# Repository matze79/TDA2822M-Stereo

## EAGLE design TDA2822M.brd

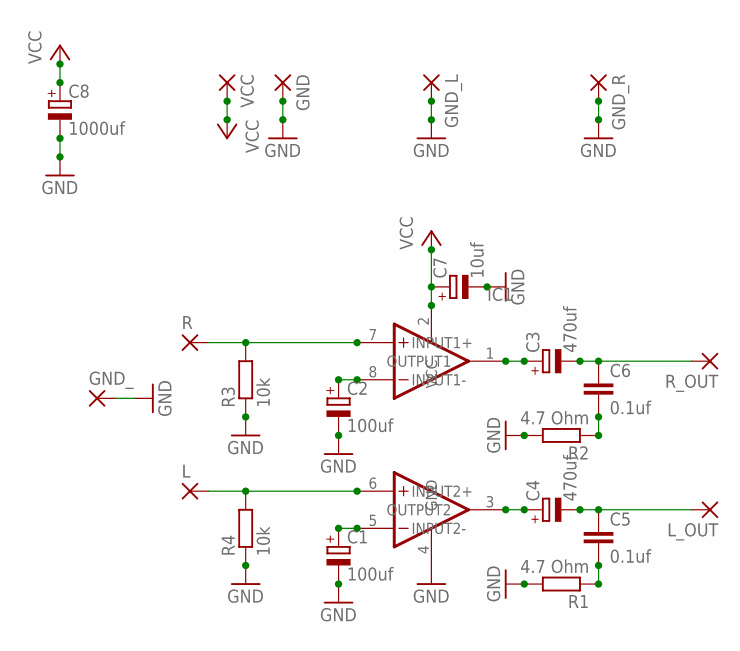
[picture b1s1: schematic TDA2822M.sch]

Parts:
C1, C2: 100uf; E2,5-6
C3, C4: 470uf; E2,5-6
C5, C6: 0.1uf; C025-030X050
C7: 10uf; E2,5-6
C8: 1000uf; E5-8,5
GND: 2,54/1,1
GND_: 2,54/1,1
GND_L: 2,54/1,1
GND_R: 2,54/1,1
IC1: TDA2822M; DIL8
L: 2,54/1,1
L_OUT: 2,54/1,1
R: 2,54/1,1
R1, R2: 4.7 Ohm; 0204/7
R3, R4: 10k; 0204/7
R_OUT: 2,54/1,1
VCC: 2,54/1,1

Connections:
GND: C1.-, C2.-, C7.-, C8.-, GND.1, GND_.1, GND_L.1, GND_R.1, IC1.4 (GND), R1.2, R2.2, R3.1, R4.1
unnamed: C1.+, IC1.5 (INPUT2-)
unnamed: C2.+, IC1.8 (INPUT1-)
unnamed: IC1.6 (INPUT2+), L.1, R4.2
unnamed: IC1.7 (INPUT1+), R.1, R3.2
unnamed: C3.+, IC1.1 (OUTPUT1)
unnamed: C4.-, C5.1, L_OUT.1
unnamed: C5.2, R1.1
unnamed: C4.+, IC1.3 (OUTPUT2)
unnamed: C3.-, C6.1, R_OUT.1
unnamed: C6.2, R2.1
VCC: C7.+, C8.+, IC1.2 (VCC), VCC.1

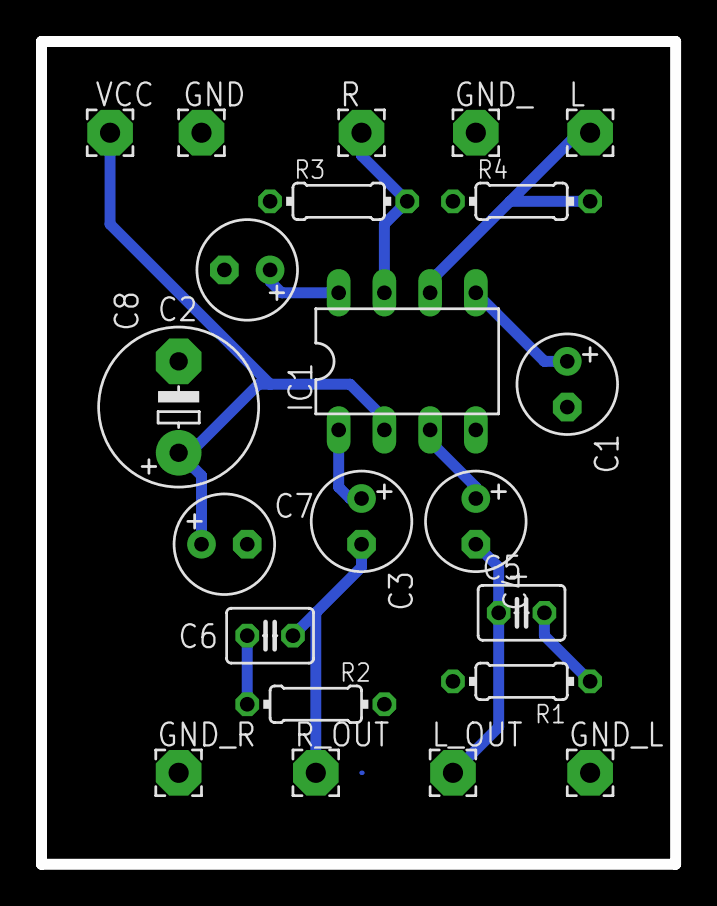
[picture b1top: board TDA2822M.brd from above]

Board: 2 copper layers, 35.2 x 45.7 mm, 22 parts (0 on the bottom side), 12 nets.
